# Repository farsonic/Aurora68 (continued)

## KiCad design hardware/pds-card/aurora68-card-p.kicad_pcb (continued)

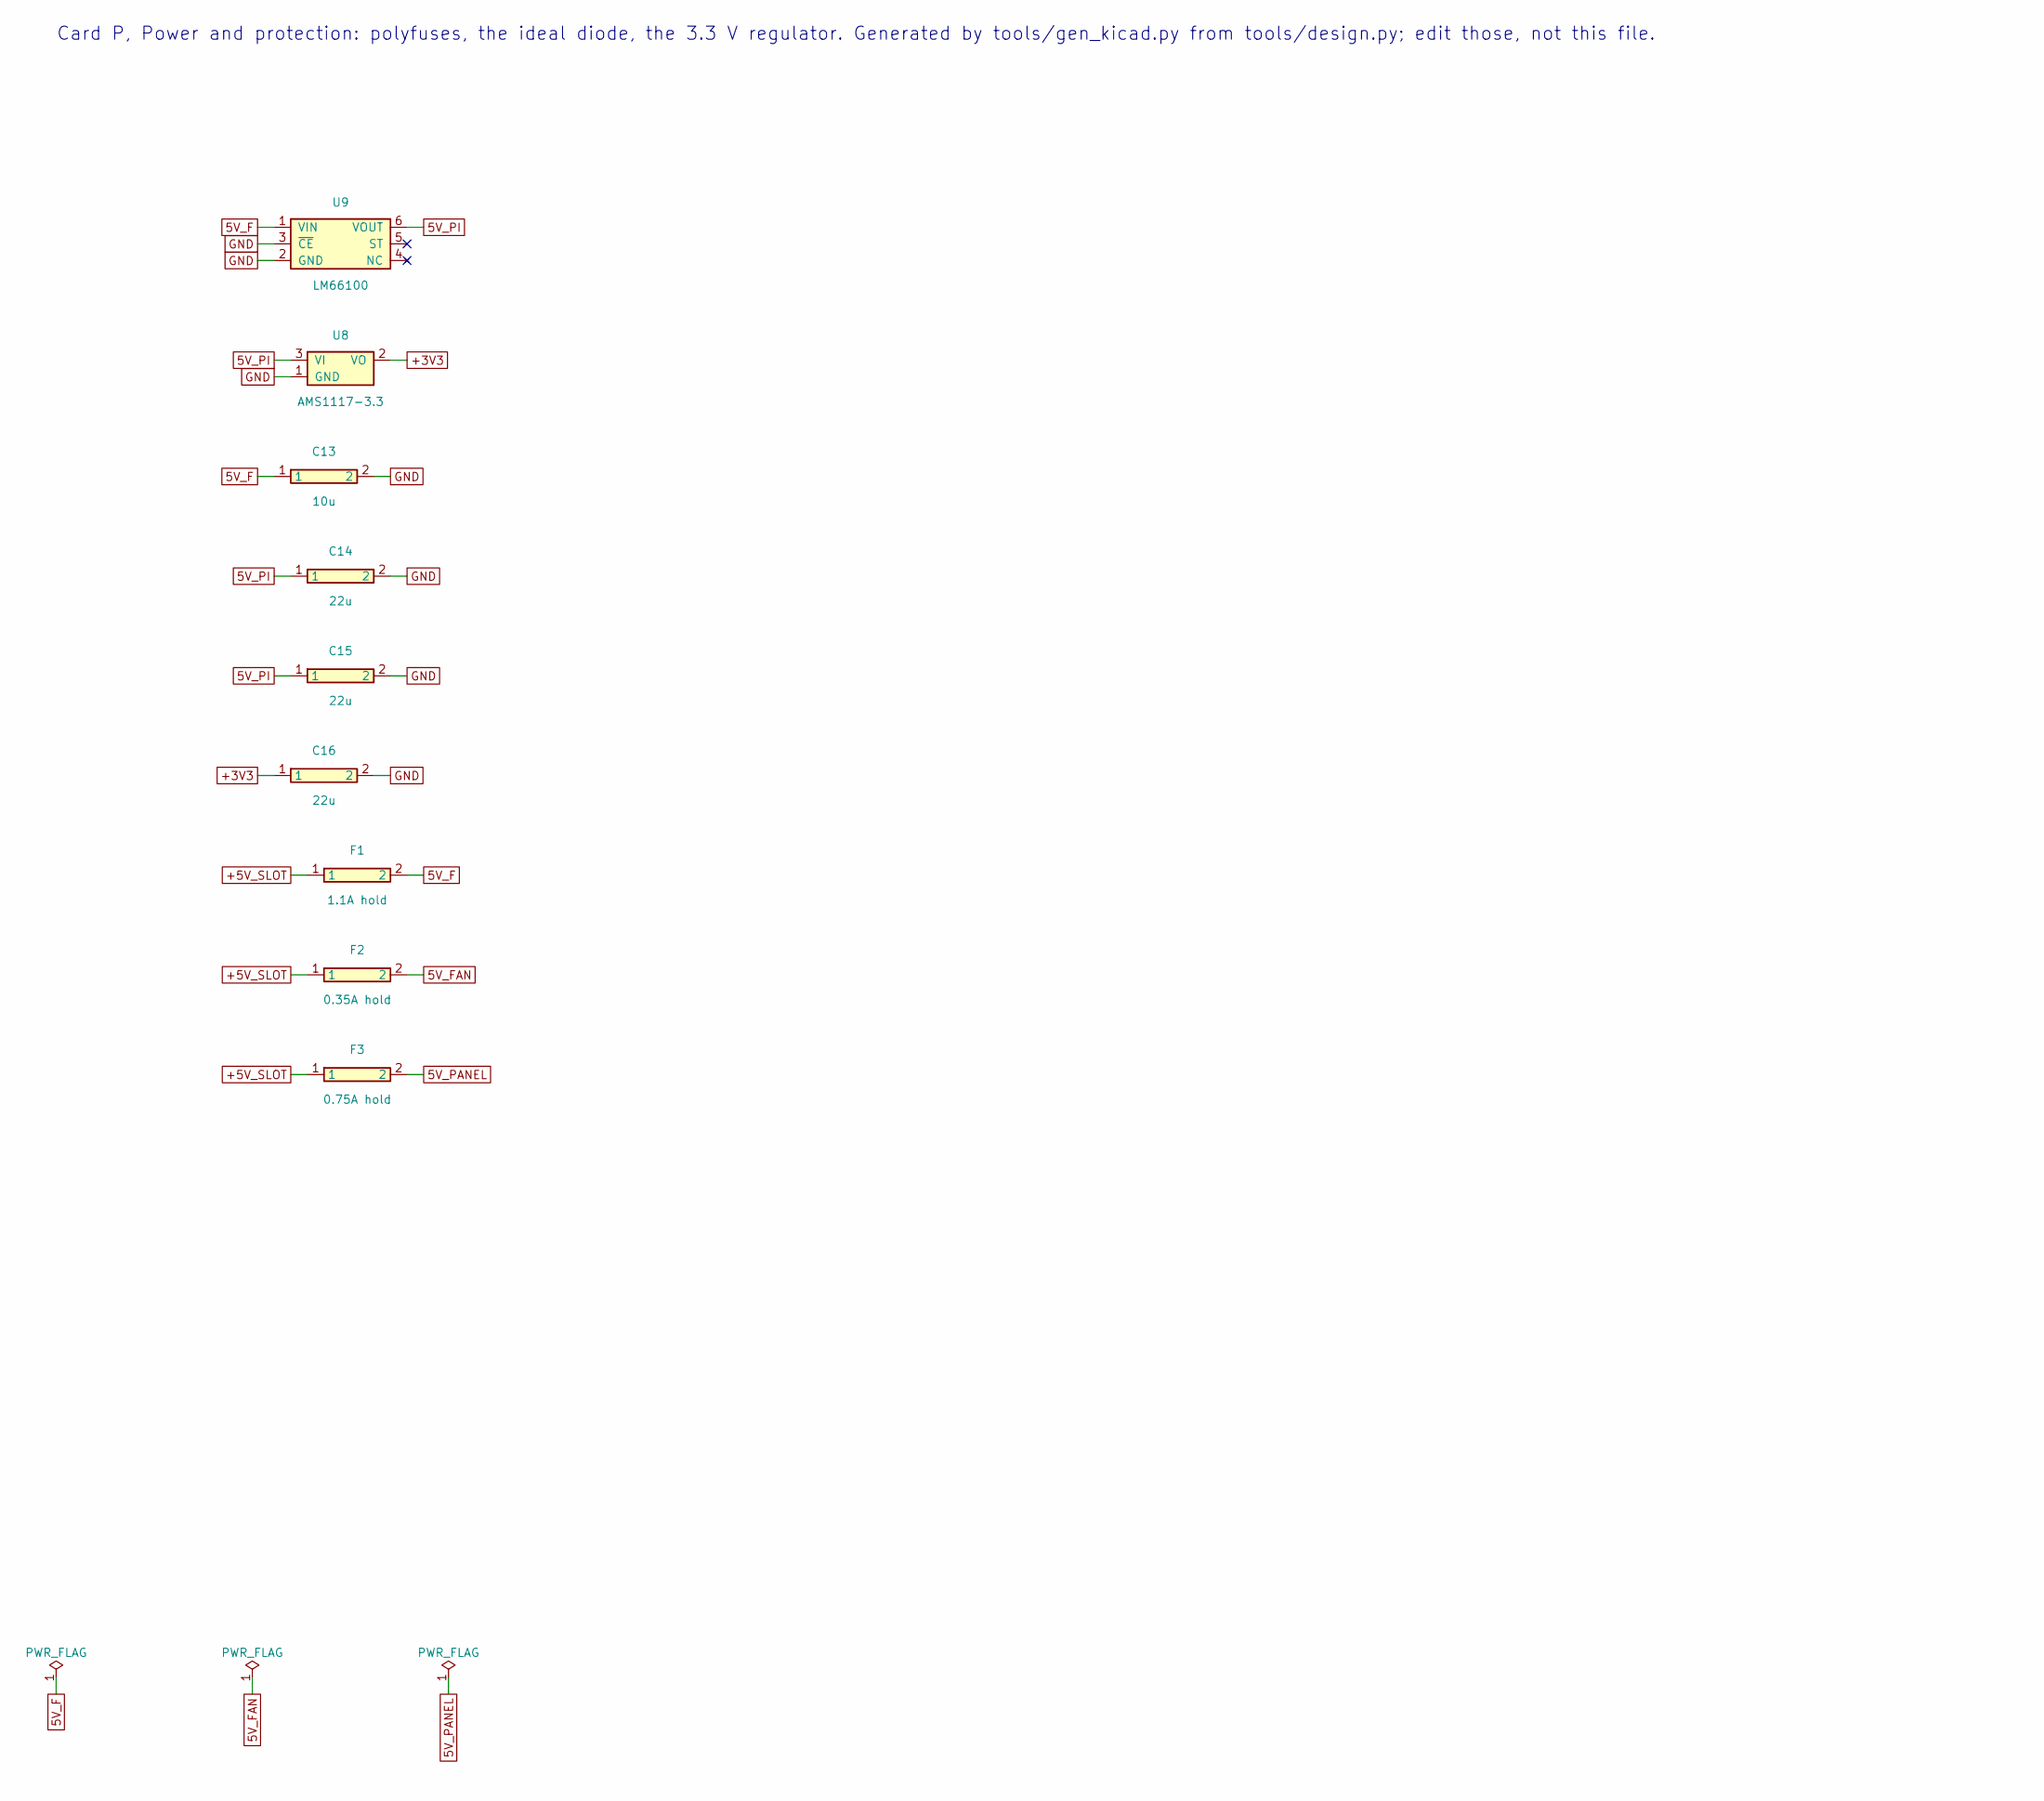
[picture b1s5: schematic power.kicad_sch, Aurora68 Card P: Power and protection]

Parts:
C13: 10u; C_0805_2012Metric; LCSC C15850
C14, C15, C16: 22u; C_0805_2012Metric; LCSC C45783
F1: 1.1A hold; Fuse_1812_4532Metric; MPN PTC 1812, 1.1 A hold, 2.2 A trip, 6 V o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
F2: 0.35A hold; Fuse_1206_3216Metric; MPN PTC 1206, 0.35 A hold, 6 V or more
F3: 0.75A hold; Fuse_1812_4532Metric; MPN PTC 1812, 0.75 A hold (Apple allows 750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
U8: AMS1117-3.3; SOT-223-3_TabPin2; LCSC C6186
U9: LM66100; SOT-363_SC-70-6; MPN LM66100DCKR

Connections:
5V_F: C13.1, F1.2, U9.1
5V_FAN: F2.2; also elsewhere on the board
5V_PANEL: F3.2; also elsewhere on the board
5V_PI: C14.1, C15.1, U8.3, U9.6; also elsewhere on the board
+3V3: C16.1, U8.2; also elsewhere on the board
+5V_SLOT: F1.1, F2.1, F3.1; also elsewhere on the board
GND: C13.2, C14.2, C15.2, C16.2, U8.1, U9.2, U9.3; also elsewhere on the board

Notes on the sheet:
Card P, Power and protection: polyfuses, the ideal diode, the 3.3 V regulator. Generated by tools/gen_kicad.py from tools/design.py; edit those, not this file.

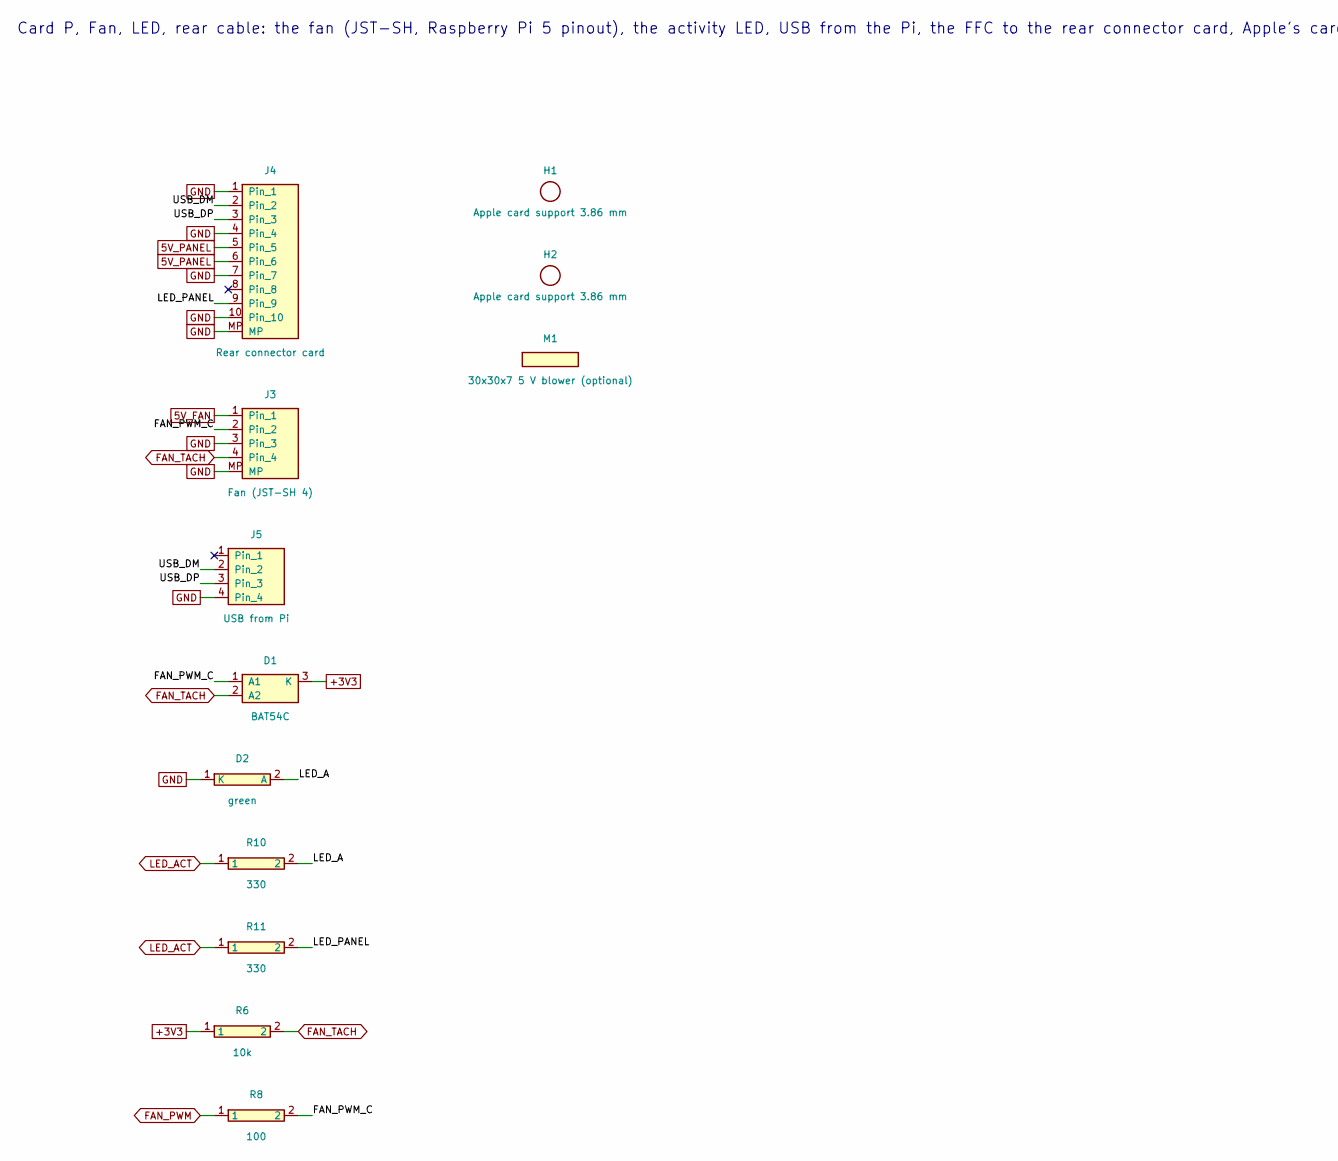
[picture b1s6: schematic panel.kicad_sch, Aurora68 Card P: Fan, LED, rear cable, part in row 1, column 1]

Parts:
D1: BAT54C; SOT-23; MPN BAT54C (common cathode)
D2: green; LED_0603_1608Metric
H1, H2: Apple card support 3.86 mm; Aurora68_AppleCardSupport_3.86mm
J3: Fan (JST-SH 4); JST_SH_SM04B-SRSS-TB_1x04-1MP_P1.00mm_Horizontal; MPN JST SM04B-SRSS-TB(LF)(SN); LCSC C160390
J4: Rear connector card; TE_1-84952-0_1x10-1MP_P1.0mm_Horizontal; MPN TE 1-84952-0 (FFC 1.0 mm, 10 positions,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
J5: USB from Pi; PinHeader_1x04_P2.54mm_Horizontal
M1: 30x30x7 5 V blower (optional); Aurora68_Fan_Blower_30x30_3xM2; MPN 30 x 30 x 7 mm 5 V blower, about 0.2 A,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
R6: 10k; R_0603_1608Metric; LCSC C25804
R8: 100; R_0603_1608Metric; LCSC C22775
R10, R11: 330; R_0603_1608Metric; LCSC C23138

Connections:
5V_FAN: J3.1; also elsewhere on the board
5V_PANEL: J4.5, J4.6; also elsewhere on the board
+3V3: D1.3, R6.1; also elsewhere on the board
FAN_PWM: R8.1; also elsewhere on the board
FAN_PWM_C: D1.1, J3.2, R8.2
FAN_TACH: D1.2, J3.4, R6.2; also elsewhere on the board
GND: D2.1, J3.3, J3.MP, J4.1, J4.4, J4.7, J4.10, J4.MP, J5.4; also elsewhere on the board
LED_A: D2.2, R10.2
LED_ACT: R10.1, R11.1; also elsewhere on the board
LED_PANEL: J4.9, R11.2
USB_DM: J4.2, J5.2
USB_DP: J4.3, J5.3

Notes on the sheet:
Card P, Fan, LED, rear cable: the fan (JST-SH, Raspberry Pi 5 pinout), the activity LED, USB from the Pi, the FFC to the rear connector card, Apple's card supports. Generated by tools/gen_kicad.py from tools/design.py; edit those, not this file.

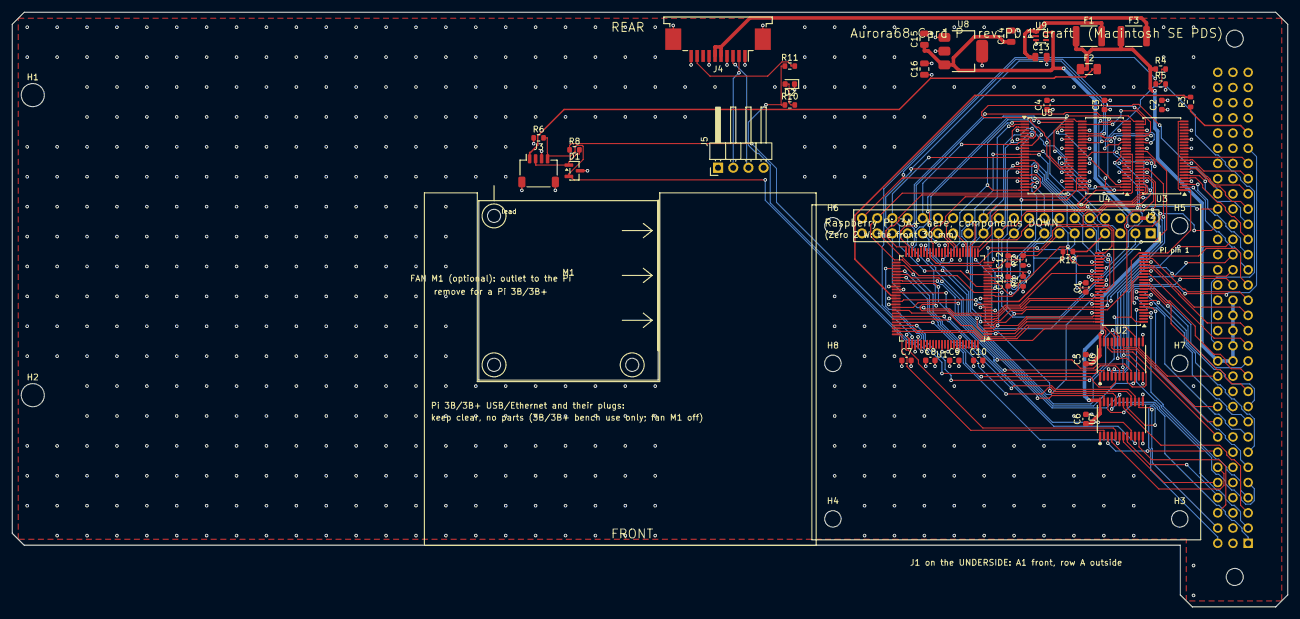
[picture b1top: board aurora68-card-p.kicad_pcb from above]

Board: 4 copper layers, 213.2 x 99.4 mm, 54 parts (1 on the bottom side), 135 nets.

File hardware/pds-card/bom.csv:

References,Qty,Value,Footprint,Description,MPN / requirement,LCSC,Assembly,Height_mm,Note
C1 C2 C3 C4 C5 C6 C7 C8 C9 C10 C11 C12,12,100n,C_0603_1608Metric,Capacitor,,C14663,SMD (top),0.90,"CPLD VCCIO/VCCINT decoupling (PiStorm C7-C10, C13, C14); latch decoupling (PiStorm C1-C4)"
C13,1,10u,C_0805_2012Metric,Capacitor,,C15850,SMD (top),1.45,
C14 C15 C16,3,22u,C_0805_2012Metric,Capacitor,,C45783,SMD (top),1.45,PiStorm C11; PiStorm C12
D1,1,BAT54C,SOT-23,"Dual Schottky diode, common cathode, SOT-23 (1 A1, 2 A2, 3 K)",BAT54C (common cathode),,SMD (top),1.25,clamps the fan's PWM and TACH to 3.3 V (LCSC number to choose)
D2,1,green,LED_0603_1608Metric,LED,,,SMD (top),0.80,activity
F1,1,1.1A hold,Fuse_1812_4532Metric,Resettable fuse (PTC),"PTC 1812, 1.1 A hold, 2.2 A trip, 6 V or more (e.g. Bourns MF-MSMF110-2)",,SMD (top),1.80,
F2,1,0.35A hold,Fuse_1206_3216Metric,Resettable fuse (PTC),"PTC 1206, 0.35 A hold, 6 V or more",,SMD (top),1.30,
F3,1,0.75A hold,Fuse_1812_4532Metric,Resettable fuse (PTC),"PTC 1812, 0.75 A hold (Apple allows 750 mA at +5 V for a peripheral outside the case)",,SMD (top),1.80,
H1 H2,2,Apple card support 3.86 mm,Aurora68_AppleCardSupport_3.86mm,"Mounting hole, no connection",,,none (drilled hole),0.00,
H3 H4 H5 H6,4,M2.5 standoff 8.5 mm,Aurora68_PiStandoff_M2.5,"Mounting hole, no connection",,,none (drilled hole),0.00,
H7 H8,2,M2.5 standoff 8.5 mm (Zero 2 W),Aurora68_PiStandoff_M2.5,"Mounting hole, no connection",,,none (drilled hole),0.00,
J1,1,DIN 41612 C 96 male straight press-fit,Aurora68_DIN41612_C_3x32_Male_Straight_PressFit_Bottom,"The Macintosh SE's 96-pin processor direct slot, the card's plug (pin names from se-pds-pinout.csv)","DIN 41612 type C, 3x32 (a+b+c), male, straight, press-fit (e.g. ERNI 024393 / Harting 09 03 296 68xx; verify)",,through-hole,1.50,
J2,1,Pi socket 2x20 6.0 mm,Aurora68_PiSocket_2x20_Inverted,2x20 socket for a Raspberry Pi 3A+ / Zero 2 W turned components-down (pin names as on the Pi),"2x20 female socket, 2.54 mm, 6.0 mm body, open-bottom contacts accepting 6.0 mm pins (choose; README)",,through-hole,6.00,
J3,1,Fan (JST-SH 4),JST_SH_SM04B-SRSS-TB_1x04-1MP_P1.00mm_Horizontal,"Connector, 4 positions, 1.0 mm (JST-SH), with mounting pads",JST SM04B-SRSS-TB(LF)(SN),C160390,SMD (top),3.00,"the Raspberry Pi 5 FAN pinout: 1 +5 V, 2 PWM, 3 GND, 4 tachometer (LCSC number to confirm)"
J4,1,Rear connector card,TE_1-84952-0_1x10-1MP_P1.0mm_Horizontal,"FFC/FPC connector, 10 positions, 1.0 mm, with mounting pads","TE 1-84952-0 (FFC 1.0 mm, 10 positions, ZIF)",,SMD (top),2.60,
J5,1,USB from Pi,PinHeader_1x04_P2.54mm_Horizontal,Header 1x04,,,through-hole,3.80,"a short pigtail from the Pi 3A+'s USB socket, which faces it, with a right-angle USB-A plug whose cable leaves towards the rear (the fan is beside it); pin 1 (VBUS) deliberately not connected"
M1,1,30x30x7 5 V blower (optional),Aurora68_Fan_Blower_30x30_3xM2,"30 mm 5 V blower fan, held by three M2 screws; its lead plugs into J3","30 x 30 x 7 mm 5 V blower, about 0.2 A, PWM and tachometer, JST-SH 4-pin lead of 60 mm or more (the owner's; Raspberry Pi 5 fan pinout); three M2 screws or plastic pins",,"optional, fitted by hand (M2 screws)",7.50,"optional, fitted by hand; outlet towards the Pi; remove it to use a 3B/3B+ on the bench"
R1 R2,2,4.7k,R_0603_1608Metric,Resistor,,C23162,SMD (top),0.55,TDI pull-up (PiStorm R1); TMS pull-up (PiStorm R2)
R3 R12,2,22,R_0603_1608Metric,Resistor,,C23345,SMD (top),0.55,"C8M into the CPLD, as the PiStorm's 68000 clock (its R3); GPCLK0 (200 MHz) series resistor at the source, beside the Pi's pin 7 (fit 0 ohm for the PiStorm's direct wire)"
R4 R6,2,10k,R_0603_1608Metric,Resistor,,C25804,SMD (top),0.55,SE power sense: 5 V -> 3.0 V; tachometer pull-up
R5,1,15k,R_0603_1608Metric,Resistor,,C22809,SMD (top),0.55,
R8,1,100,R_0603_1608Metric,Resistor,,C22775,SMD (top),0.55,"fan PWM from the CPLD, series"
R10 R11,2,330,R_0603_1608Metric,Resistor,,C23138,SMD (top),0.55,"the connector card's LED, over the cable"
U1,1,EPM240T100C5N,TQFP-100_14x14mm_P0.5mm,"Altera/Intel MAX II CPLD, TQFP-100: EPM240T100C5N, or EPM570T100C5N (pins 37, 39, 88, 90 are its GNDINT/VCCINT; an EPM240 leaves them as unused I/O, so the PiStorm-style footprint takes both)","EPM240T100C5N (or EPM570T100C5N, LCSC C40067, if the fitter needs more than 240 LEs)",,SMD (top),1.60,
U2 U3 U4 U5,4,74LVC16373,TSSOP-48_6.1x12.5mm_P0.5mm,"16-bit transparent D-type latch, 3-state, 5 V tolerant (74LVC16373A)",SN74LVC16373ADGGR,,SMD (top),1.20,
U6 U7,2,SN74CBTD3384PW,TSSOP-24_4.4x7.8mm_P0.65mm,10-bit FET bus switch with level shifting (as the PiStorm Rev B),SN74CBTD3384PWR,C7155,SMD (top),1.20,
U8,1,AMS1117-3.3,SOT-223-3_TabPin2,"1 A 3.3 V LDO, SOT-223 (the PiStorm uses an LM1117-3.3 in the same place)",,C6186,SMD (top),1.80,PiStorm U8 (LM1117-3.3)
U9,1,LM66100,SOT-363_SC-70-6,"Ideal diode, 1.5 A, 5.5 V, reverse-current blocking",LM66100DCKR,,SMD (top),1.10,ideal diode: a Pi powered from its own USB never feeds the SE

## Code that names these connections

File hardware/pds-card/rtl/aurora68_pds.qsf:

# SPDX-License-Identifier: MIT
# aurora68_pds.qsf - pin assignments for Card P's CPLD, written by tools/gen_kicad.py from tools/design.py
# (the same table the schematic is drawn from). Every signal the classic PiStorm has is on the PiStorm's
# own pin (reference/pistorm/rtl/pistorm.qsf); the slot card's new signals are on pins the PiStorm leaves free.
# The footprint is wired like the PiStorm's for an EPM570 (pins 37, 39, 88, 90 power), which an EPM240
# also fits (those pins are I/O on the EPM240 and are left unused): try the EPM240 first.
set_global_assignment -name FAMILY "MAX II"
set_global_assignment -name DEVICE EPM240T100C5
set_global_assignment -name TOP_LEVEL_ENTITY aurora68_pds
set_global_assignment -name VERILOG_FILE aurora68_pds.v
set_global_assignment -name SDC_FILE aurora68_pds.sdc
set_global_assignment -name RESERVE_ALL_UNUSED_PINS "AS INPUT TRI-STATED WITH WEAK PULL-UP"
set_global_assignment -name RESERVE_PIN "AS INPUT TRI-STATED" -to 37
set_global_assignment -name STRATIX_DEVICE_IO_STANDARD "3.3-V LVTTL"
set_global_assignment -name POWER_UP_LEVEL "AS SPECIFIED IN DESIGN"

set_location_assignment PIN_2 -to PI_D[0]
set_location_assignment PIN_3 -to PI_D[1]
set_location_assignment PIN_4 -to PI_D[2]
set_location_assignment PIN_5 -to PI_D[3]
set_location_assignment PIN_6 -to PI_D[4]
set_location_assignment PIN_7 -to PI_D[5]
set_location_assignment PIN_8 -to PI_D[11]
set_location_assignment PIN_12 -to PI_CLK
set_location_assignment PIN_14 -to PI_D[13]
set_location_assignment PIN_15 -to PI_D[12]
set_location_assignment PIN_16 -to PI_D[9]
set_location_assignment PIN_17 -to PI_D[8]
set_location_assignment PIN_18 -to PI_D[15]
set_location_assignment PIN_19 -to PI_D[14]
set_location_assignment PIN_20 -to PI_D[10]
set_location_assignment PIN_21 -to PI_D[7]
set_location_assignment PIN_26 -to PI_D[6]
set_location_assignment PIN_27 -to PI_A[0]
set_location_assignment PIN_28 -to PI_A[1]
set_location_assignment PIN_29 -to PI_WR
set_location_assignment PIN_30 -to PI_TXN_IN_PROGRESS
set_location_assignment PIN_33 -to PI_IPL_ZERO
set_location_assignment PIN_34 -to PI_RESET
set_location_assignment PIN_35 -to PI_RD
set_location_assignment PIN_36 -to LTCH_D_WR_U
set_location_assignment PIN_38 -to LTCH_D_RD_OE_n
set_location_assignment PIN_40 -to LTCH_D_WR_L
set_location_assignment PIN_41 -to LTCH_D_WR_OE_n
set_location_assignment PIN_42 -to LTCH_A_8
set_location_assignment PIN_43 -to LTCH_A_OE_n
set_location_assignment PIN_44 -to LTCH_A_0
set_location_assignment PIN_47 -to LTCH_A_16
set_location_assignment PIN_48 -to LTCH_A_24
set_location_assignment PIN_49 -to LTCH_D_RD_L
set_location_assignment PIN_50 -to LTCH_D_RD_U
set_location_assignment PIN_52 -to M68K_VMA_n
set_location_assignment PIN_53 -to M68K_E    # the PiStorm's E pin (an output there)
set_location_assignment PIN_54 -to M68K_VPA_n
set_location_assignment PIN_55 -to M68K_BERR_n
set_location_assignment PIN_56 -to M68K_IPL_n[0]
set_location_assignment PIN_57 -to M68K_FC[2]
set_location_assignment PIN_58 -to M68K_IPL_n[1]
set_location_assignment PIN_61 -to M68K_IPL_n[2]
set_location_assignment PIN_62 -to M68K_CLK    # the PiStorm's M68K_CLK pin, through 22 ohm as there
set_location_assignment PIN_64 -to M68K_FC[1]
set_location_assignment PIN_66 -to M68K_FC[0]
set_location_assignment PIN_67 -to M68K_RESET_n
set_location_assignment PIN_69 -to M68K_BR_n    # the PiStorm's /BR pin (an input there)
set_location_assignment PIN_70 -to M68K_BGACK_n
set_location_assignment PIN_71 -to M68K_BG_n    # the PiStorm's /BG pin (an output there)
set_location_assignment PIN_72 -to M68K_AS_n
set_location_assignment PIN_73 -to M68K_UDS_n
set_location_assignment PIN_74 -to M68K_LDS_n
set_location_assignment PIN_75 -to M68K_RW
set_location_assignment PIN_76 -to M68K_DTACK_n
set_location_assignment PIN_77 -to SLOT_PWR
set_location_assignment PIN_78 -to FAN_PWM
set_location_assignment PIN_81 -to FAN_TACH
set_location_assignment PIN_83 -to LED_ACT
set_global_assignment -name USE_CONFIGURATION_DEVICE OFF
